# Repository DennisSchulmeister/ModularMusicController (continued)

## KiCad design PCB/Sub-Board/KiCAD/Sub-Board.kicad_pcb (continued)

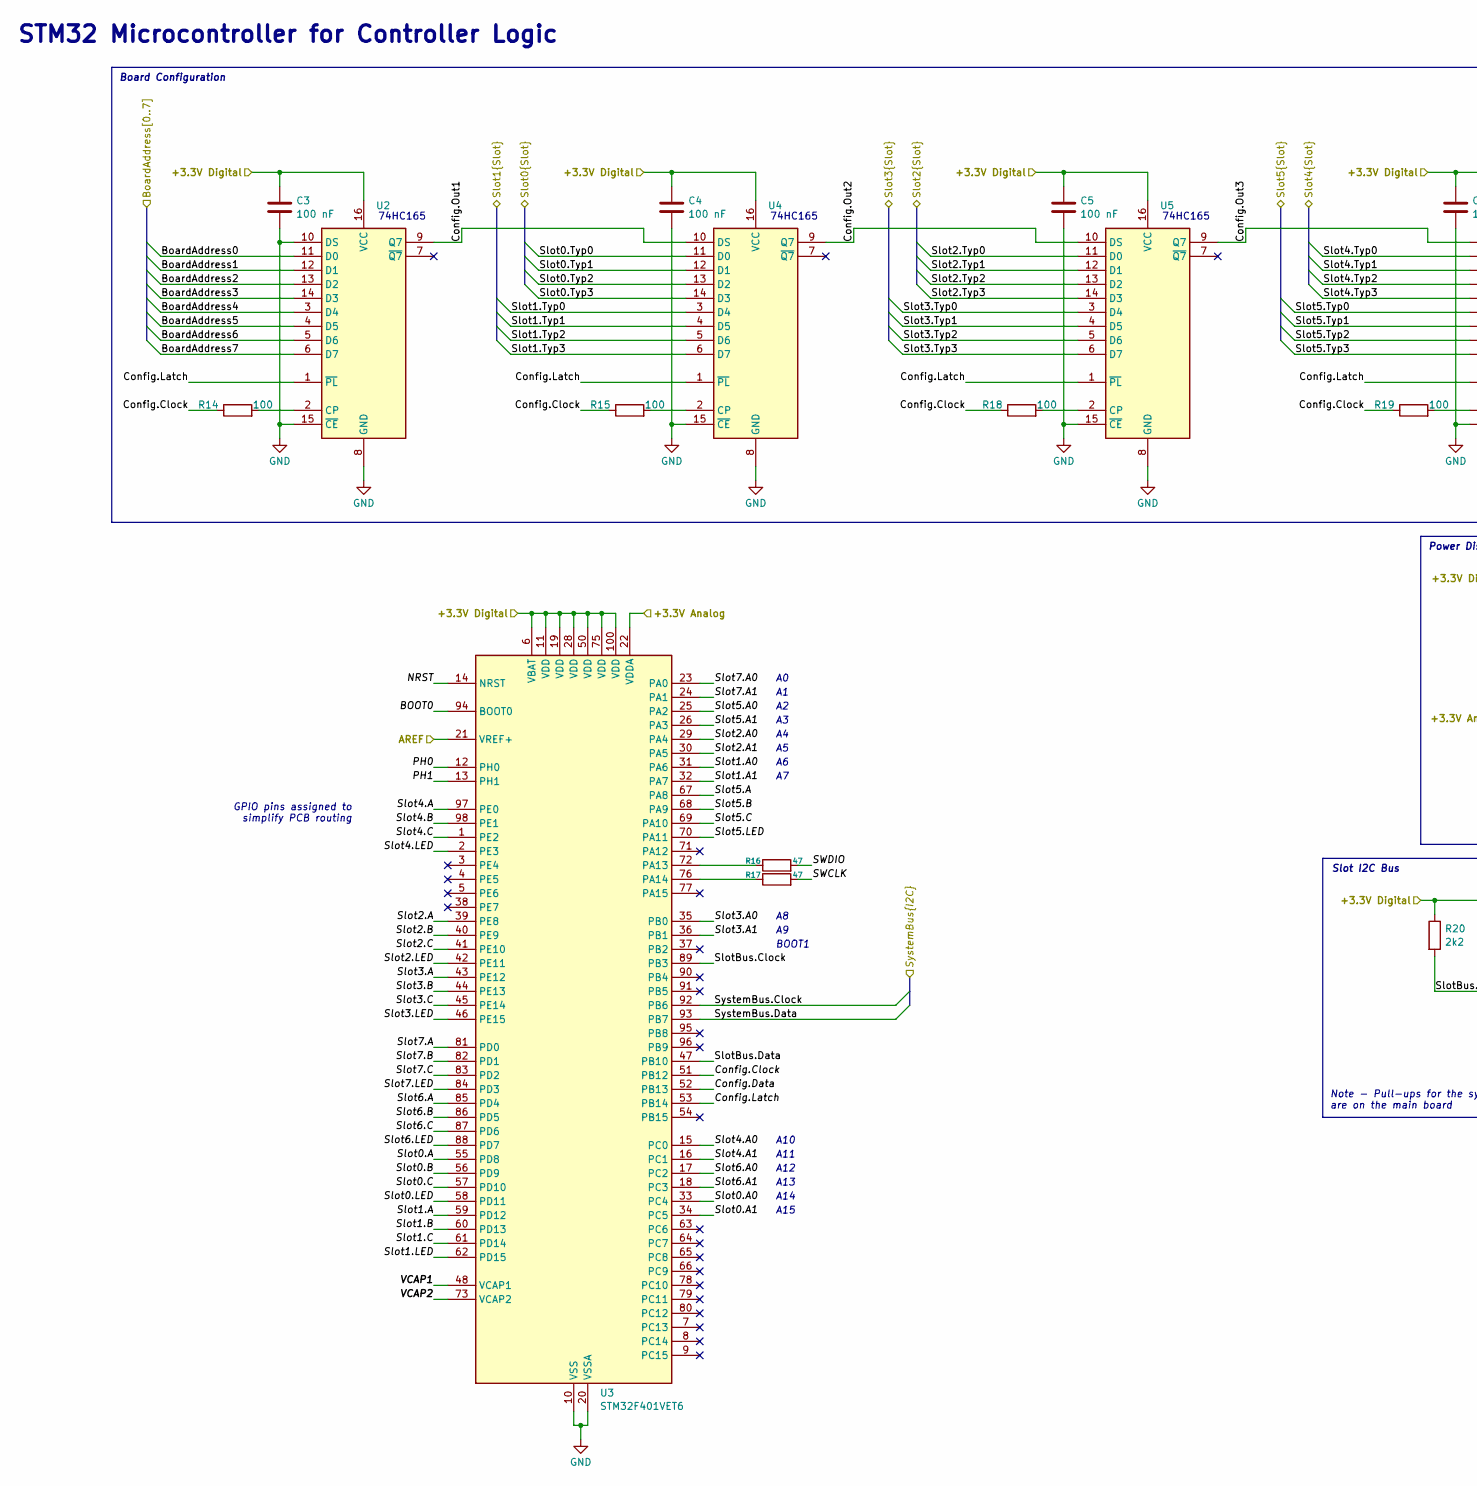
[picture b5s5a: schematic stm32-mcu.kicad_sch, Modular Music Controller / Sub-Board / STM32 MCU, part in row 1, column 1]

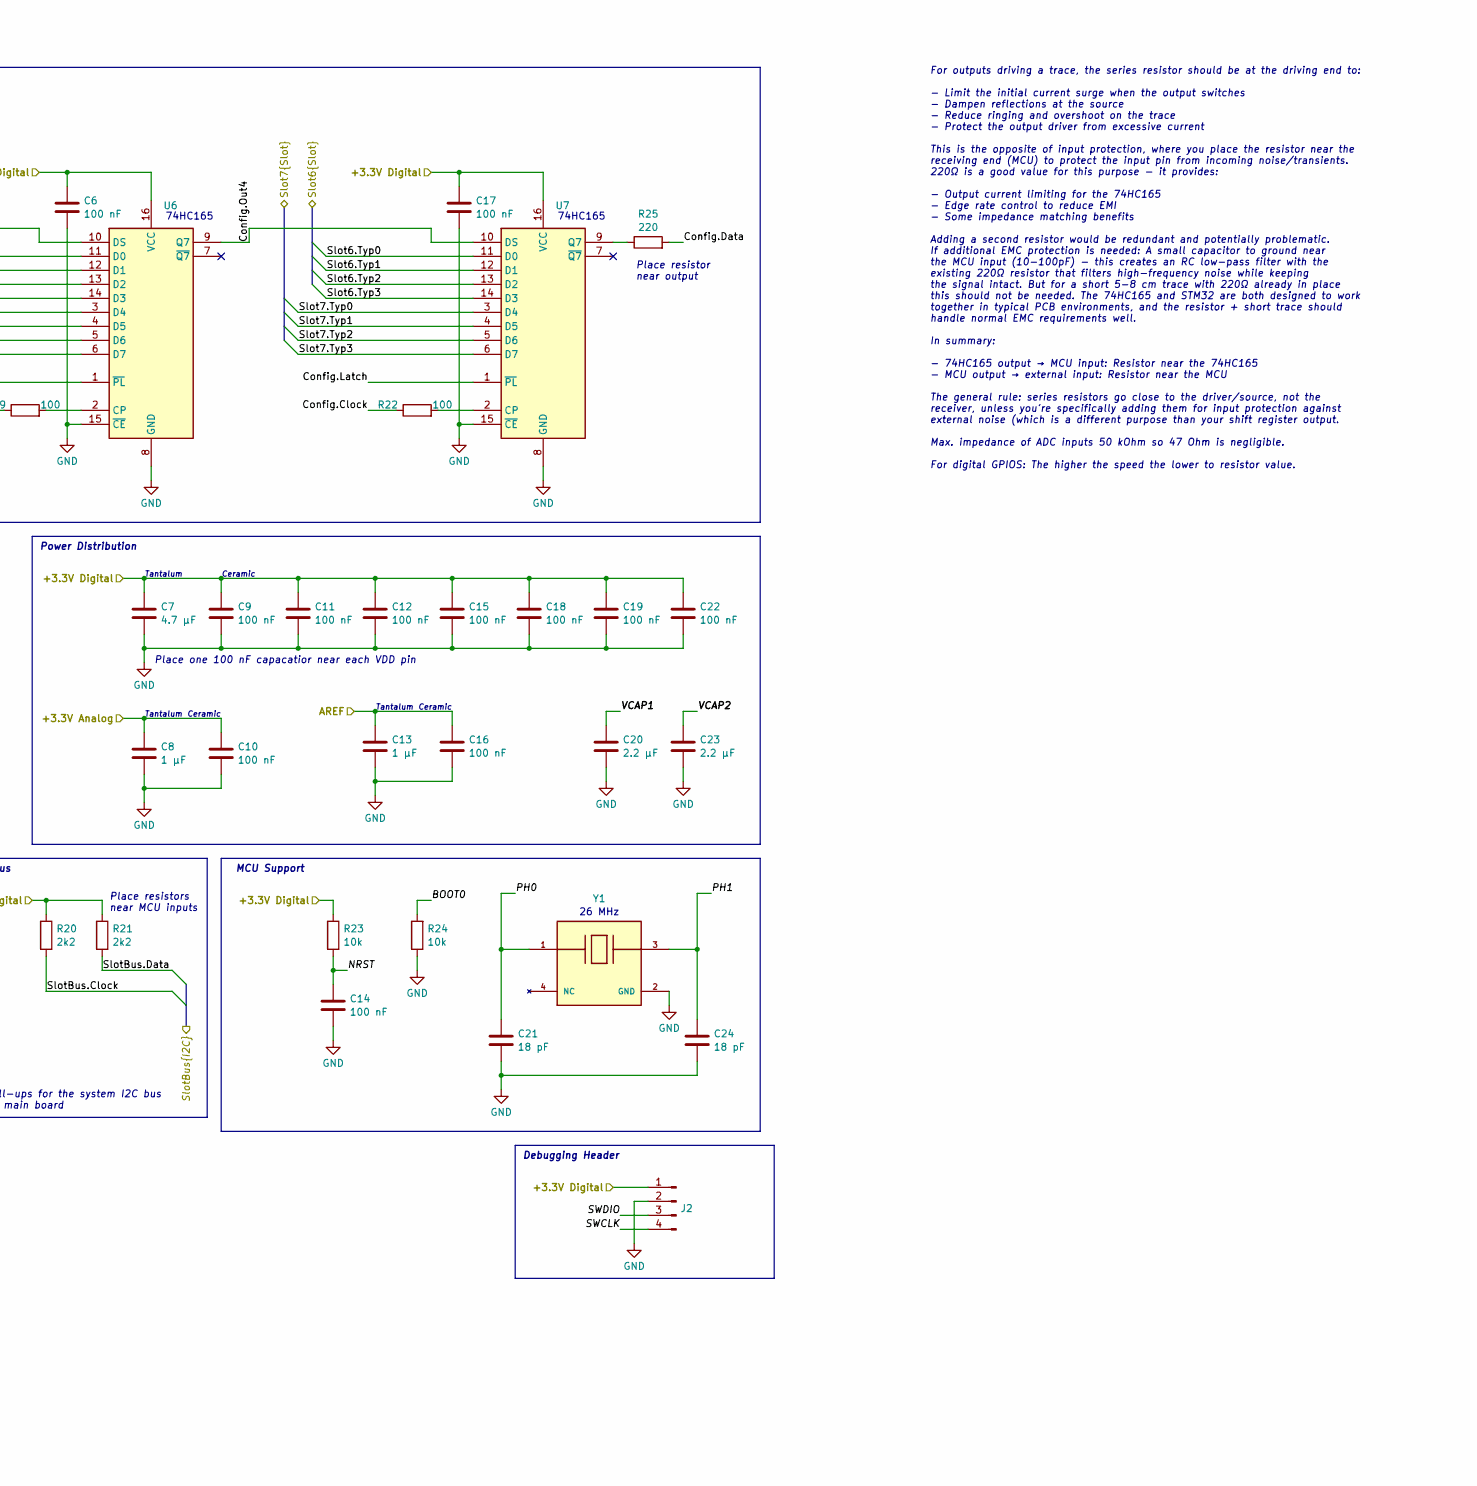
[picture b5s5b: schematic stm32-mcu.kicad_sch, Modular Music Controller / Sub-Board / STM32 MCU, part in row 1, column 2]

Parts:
C3, C4, C5, C6, C9, C10, C11, C12, C14, C15, C16, C17, C18, C19, C22: 100 nF; C_0603_1608Metric
C7: 4.7 µF; C_0805_2012Metric
C8, C13: 1 µF; C_0805_2012Metric
C20, C23: 2.2 µF; C_0805_2012Metric
C21, C24: 18 pF; C_0603_1608Metric
J2: Harwin M20-8770446; PinHeader_1x04_P2.54mm_Vertical_SMD_Pin1Right
R14, R15, R18, R19, R22: 100; R_0402_1005Metric
R16, R17: 47; R_0402_1005Metric
R20, R21: 2k2; R_0402_1005Metric
R23, R24: 10k; R_0402_1005Metric
R25: 220; R_0402_1005Metric
U2, U4, U5, U6, U7: Nexperia 74HC165PW,118; TSSOP-16_4.4x5mm_P0.65mm
U3: STM32F401VET6; LQFP-100_14x14mm_P0.5mm
Y1: Kyocera CX2016DB26000H0FLJC2; OSC_CX2016DB26000H0FLJC2; PARTREV October 2024

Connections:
/Board Address/+3.3V Digital: C3.1, C4.1, C5.1, C6.1, C7.1, C9.1, C11.1, C12.1, C15.1, C17.1, C18.1, C19.1, C22.1, J2.1, R20.1, R21.1, R23.1, U2.16 (VCC), U3.6 (VBAT), U3.11 (VDD), U3.19 (VDD), U3.28 (VDD), U3.50 (VDD), U3.75 (VDD), U3.100 (VDD), U4.16 (VCC), U5.16 (VCC), U6.16 (VCC), U7.16 (VCC); also elsewhere on the board
/Board Address/BoardAddress0: U2.11 (D0); also elsewhere on the board
/Board Address/BoardAddress1: U2.12 (D1); also elsewhere on the board
/Board Address/BoardAddress2: U2.13 (D2); also elsewhere on the board
/Board Address/BoardAddress3: U2.14 (D3); also elsewhere on the board
/Board Address/BoardAddress4: U2.3 (D4); also elsewhere on the board
/Board Address/BoardAddress5: U2.4 (D5); also elsewhere on the board
/Board Address/BoardAddress6: U2.5 (D6); also elsewhere on the board
/Board Address/BoardAddress7: U2.6 (D7); also elsewhere on the board
/Power Supply/+3.3V Analog: C8.1, C10.1, U3.22 (VDDA); also elsewhere on the board
/Power Supply/AREF: C13.1, C16.1, U3.21 (VREF+); also elsewhere on the board
/STM32-MCU/BOOT0: R24.2, U3.94 (BOOT0)
/STM32-MCU/Config.Clock: R14.1, R15.1, R18.1, R19.1, R22.1, U3.51 (PB12)
/STM32-MCU/Config.Data: R25.2, U3.52 (PB13)
/STM32-MCU/Config.Latch: U2.1 (~PL), U3.53 (PB14), U4.1 (~PL), U5.1 (~PL), U6.1 (~PL), U7.1 (~PL)
/STM32-MCU/Config.Out1: U2.9 (Q7), U4.10 (DS)
/STM32-MCU/Config.Out2: U4.9 (Q7), U5.10 (DS)
/STM32-MCU/Config.Out3: U5.9 (Q7), U6.10 (DS)
/STM32-MCU/Config.Out4: U6.9 (Q7), U7.10 (DS)
/STM32-MCU/NRST: C14.1, R23.2, U3.14 (NRST)
/STM32-MCU/PH0: C21.1, U3.12 (PH0), Y1.1
/STM32-MCU/PH1: C24.1, U3.13 (PH1), Y1.3
/STM32-MCU/SWCLK: J2.4, R17.2
/STM32-MCU/SWDIO: J2.3, R16.2
/STM32-MCU/Slot0.A: U3.55 (PD8); also elsewhere on the board
/STM32-MCU/Slot0.A0: U3.33 (PC4); also elsewhere on the board
/STM32-MCU/Slot0.A1: U3.34 (PC5); also elsewhere on the board
/STM32-MCU/Slot0.B: U3.56 (PD9); also elsewhere on the board
/STM32-MCU/Slot0.C: U3.57 (PD10); also elsewhere on the board
/STM32-MCU/Slot0.LED: U3.58 (PD11); also elsewhere on the board
/STM32-MCU/Slot0.Typ0: U4.11 (D0); also elsewhere on the board
/STM32-MCU/Slot0.Typ1: U4.12 (D1); also elsewhere on the board
/STM32-MCU/Slot0.Typ2: U4.13 (D2); also elsewhere on the board
/STM32-MCU/Slot0.Typ3: U4.14 (D3); also elsewhere on the board
/STM32-MCU/Slot1.A: U3.59 (PD12); also elsewhere on the board
/STM32-MCU/Slot1.A0: U3.31 (PA6); also elsewhere on the board
/STM32-MCU/Slot1.A1: U3.32 (PA7); also elsewhere on the board
/STM32-MCU/Slot1.B: U3.60 (PD13); also elsewhere on the board
/STM32-MCU/Slot1.C: U3.61 (PD14); also elsewhere on the board
/STM32-MCU/Slot1.LED: U3.62 (PD15); also elsewhere on the board
/STM32-MCU/Slot1.Typ0: U4.3 (D4); also elsewhere on the board
/STM32-MCU/Slot1.Typ1: U4.4 (D5); also elsewhere on the board
/STM32-MCU/Slot1.Typ2: U4.5 (D6); also elsewhere on the board
/STM32-MCU/Slot1.Typ3: U4.6 (D7); also elsewhere on the board
/STM32-MCU/Slot2.A: U3.39 (PE8); also elsewhere on the board
/STM32-MCU/Slot2.A0: U3.29 (PA4); also elsewhere on the board
/STM32-MCU/Slot2.A1: U3.30 (PA5); also elsewhere on the board
/STM32-MCU/Slot2.B: U3.40 (PE9); also elsewhere on the board
/STM32-MCU/Slot2.C: U3.41 (PE10); also elsewhere on the board
/STM32-MCU/Slot2.LED: U3.42 (PE11); also elsewhere on the board
/STM32-MCU/Slot2.Typ0: U5.11 (D0); also elsewhere on the board
/STM32-MCU/Slot2.Typ1: U5.12 (D1); also elsewhere on the board
/STM32-MCU/Slot2.Typ2: U5.13 (D2); also elsewhere on the board
/STM32-MCU/Slot2.Typ3: U5.14 (D3); also elsewhere on the board
/STM32-MCU/Slot3.A: U3.43 (PE12); also elsewhere on the board
/STM32-MCU/Slot3.A0: U3.35 (PB0); also elsewhere on the board
/STM32-MCU/Slot3.A1: U3.36 (PB1); also elsewhere on the board
/STM32-MCU/Slot3.B: U3.44 (PE13); also elsewhere on the board
/STM32-MCU/Slot3.C: U3.45 (PE14); also elsewhere on the board
/STM32-MCU/Slot3.LED: U3.46 (PE15); also elsewhere on the board
/STM32-MCU/Slot3.Typ0: U5.3 (D4); also elsewhere on the board
/STM32-MCU/Slot3.Typ1: U5.4 (D5); also elsewhere on the board
/STM32-MCU/Slot3.Typ2: U5.5 (D6); also elsewhere on the board
/STM32-MCU/Slot3.Typ3: U5.6 (D7); also elsewhere on the board
/STM32-MCU/Slot4.A: U3.97 (PE0); also elsewhere on the board
/STM32-MCU/Slot4.A0: U3.15 (PC0); also elsewhere on the board
/STM32-MCU/Slot4.A1: U3.16 (PC1); also elsewhere on the board
/STM32-MCU/Slot4.B: U3.98 (PE1); also elsewhere on the board
/STM32-MCU/Slot4.C: U3.1 (PE2); also elsewhere on the board
/STM32-MCU/Slot4.LED: U3.2 (PE3); also elsewhere on the board
/STM32-MCU/Slot4.Typ0: U6.11 (D0); also elsewhere on the board
/STM32-MCU/Slot4.Typ1: U6.12 (D1); also elsewhere on the board
/STM32-MCU/Slot4.Typ2: U6.13 (D2); also elsewhere on the board
/STM32-MCU/Slot4.Typ3: U6.14 (D3); also elsewhere on the board
/STM32-MCU/Slot5.A: U3.67 (PA8); also elsewhere on the board
/STM32-MCU/Slot5.A0: U3.25 (PA2); also elsewhere on the board
/STM32-MCU/Slot5.A1: U3.26 (PA3); also elsewhere on the board
/STM32-MCU/Slot5.B: U3.68 (PA9); also elsewhere on the board
/STM32-MCU/Slot5.C: U3.69 (PA10); also elsewhere on the board
/STM32-MCU/Slot5.LED: U3.70 (PA11); also elsewhere on the board
/STM32-MCU/Slot5.Typ0: U6.3 (D4); also elsewhere on the board
/STM32-MCU/Slot5.Typ1: U6.4 (D5); also elsewhere on the board
/STM32-MCU/Slot5.Typ2: U6.5 (D6); also elsewhere on the board
/STM32-MCU/Slot5.Typ3: U6.6 (D7); also elsewhere on the board
/STM32-MCU/Slot6.A: U3.85 (PD4); also elsewhere on the board
/STM32-MCU/Slot6.A0: U3.17 (PC2); also elsewhere on the board
/STM32-MCU/Slot6.A1: U3.18 (PC3); also elsewhere on the board
/STM32-MCU/Slot6.B: U3.86 (PD5); also elsewhere on the board
/STM32-MCU/Slot6.C: U3.87 (PD6); also elsewhere on the board
/STM32-MCU/Slot6.LED: U3.88 (PD7); also elsewhere on the board
/STM32-MCU/Slot6.Typ0: U7.11 (D0); also elsewhere on the board
/STM32-MCU/Slot6.Typ1: U7.12 (D1); also elsewhere on the board
/STM32-MCU/Slot6.Typ2: U7.13 (D2); also elsewhere on the board
/STM32-MCU/Slot6.Typ3: U7.14 (D3); also elsewhere on the board
/STM32-MCU/Slot7.A: U3.81 (PD0); also elsewhere on the board
/STM32-MCU/Slot7.A0: U3.23 (PA0); also elsewhere on the board
/STM32-MCU/Slot7.A1: U3.24 (PA1); also elsewhere on the board
/STM32-MCU/Slot7.B: U3.82 (PD1); also elsewhere on the board
/STM32-MCU/Slot7.C: U3.83 (PD2); also elsewhere on the board
/STM32-MCU/Slot7.LED: U3.84 (PD3); also elsewhere on the board
/STM32-MCU/Slot7.Typ0: U7.3 (D4); also elsewhere on the board
/STM32-MCU/Slot7.Typ1: U7.4 (D5); also elsewhere on the board
/STM32-MCU/Slot7.Typ2: U7.5 (D6); also elsewhere on the board
/STM32-MCU/Slot7.Typ3: U7.6 (D7); also elsewhere on the board
/STM32-MCU/SlotBus.Clock: R20.2, U3.89 (PB3); also elsewhere on the board
/STM32-MCU/SlotBus.Data: R21.2, U3.47 (PB10); also elsewhere on the board
/STM32-MCU/SystemBus.Clock: U3.92 (PB6); also elsewhere on the board
/STM32-MCU/SystemBus.Data: U3.93 (PB7); also elsewhere on the board
/STM32-MCU/VCAP1: C20.1, U3.48 (VCAP1)
/STM32-MCU/VCAP2: C23.1, U3.73 (VCAP2)
GND: C3.2, C4.2, C5.2, C6.2, C7.2, C8.2, C9.2, C10.2, C11.2, C12.2, C13.2, C14.2, C15.2, C16.2, C17.2, C18.2, C19.2, C20.2, C21.2, C22.2, C23.2, C24.2, J2.2, R24.1, U2.8 (GND), U2.10 (DS), U2.15 (~CE), U3.10 (VSS), U3.20 (VSSA), U3.27 (VSS), U3.49 (VSS), U3.74 (VSS), U3.99 (VSS), U4.8 (GND), U4.15 (~CE), U5.8 (GND), U5.15 (~CE), U6.8 (GND), U6.15 (~CE), U7.8 (GND), U7.15 (~CE), Y1.2 (GND); also elsewhere on the board
unnamed: R14.2, U2.2 (CP)
unnamed: R16.1, U3.72 (PA13)
unnamed: R17.1, U3.76 (PA14)
unnamed: R15.2, U4.2 (CP)
unnamed: R18.2, U5.2 (CP)
unnamed: R19.2, U6.2 (CP)
unnamed: R22.2, U7.2 (CP)
unnamed: R25.1, U7.9 (Q7)

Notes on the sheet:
74HC165
Place resistor near output
Place resistors near MCU inputs
Power Distribution
For outputs driving a trace, the series resistor should be at the driving end to: - Limit the initial current surge when the output switches - Dampen reflections at the source - Reduce ringing and overshoot on the trace - Protect the output driver from excessive current This is the opposite of inpu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
Debugging Header
Tantalum
A12
Board Configuration
A10
Ceramic
GPIO pins assigned to simplify PCB routing
A14
A15
Place one 100 nF capacatior near each VDD pin
STM32 Microcontroller for Controller Logic
MCU Support
Slot I2C Bus
A13
A11
BOOT1
Note - Pull-ups for the system I2C bus are on the main board
26 MHz

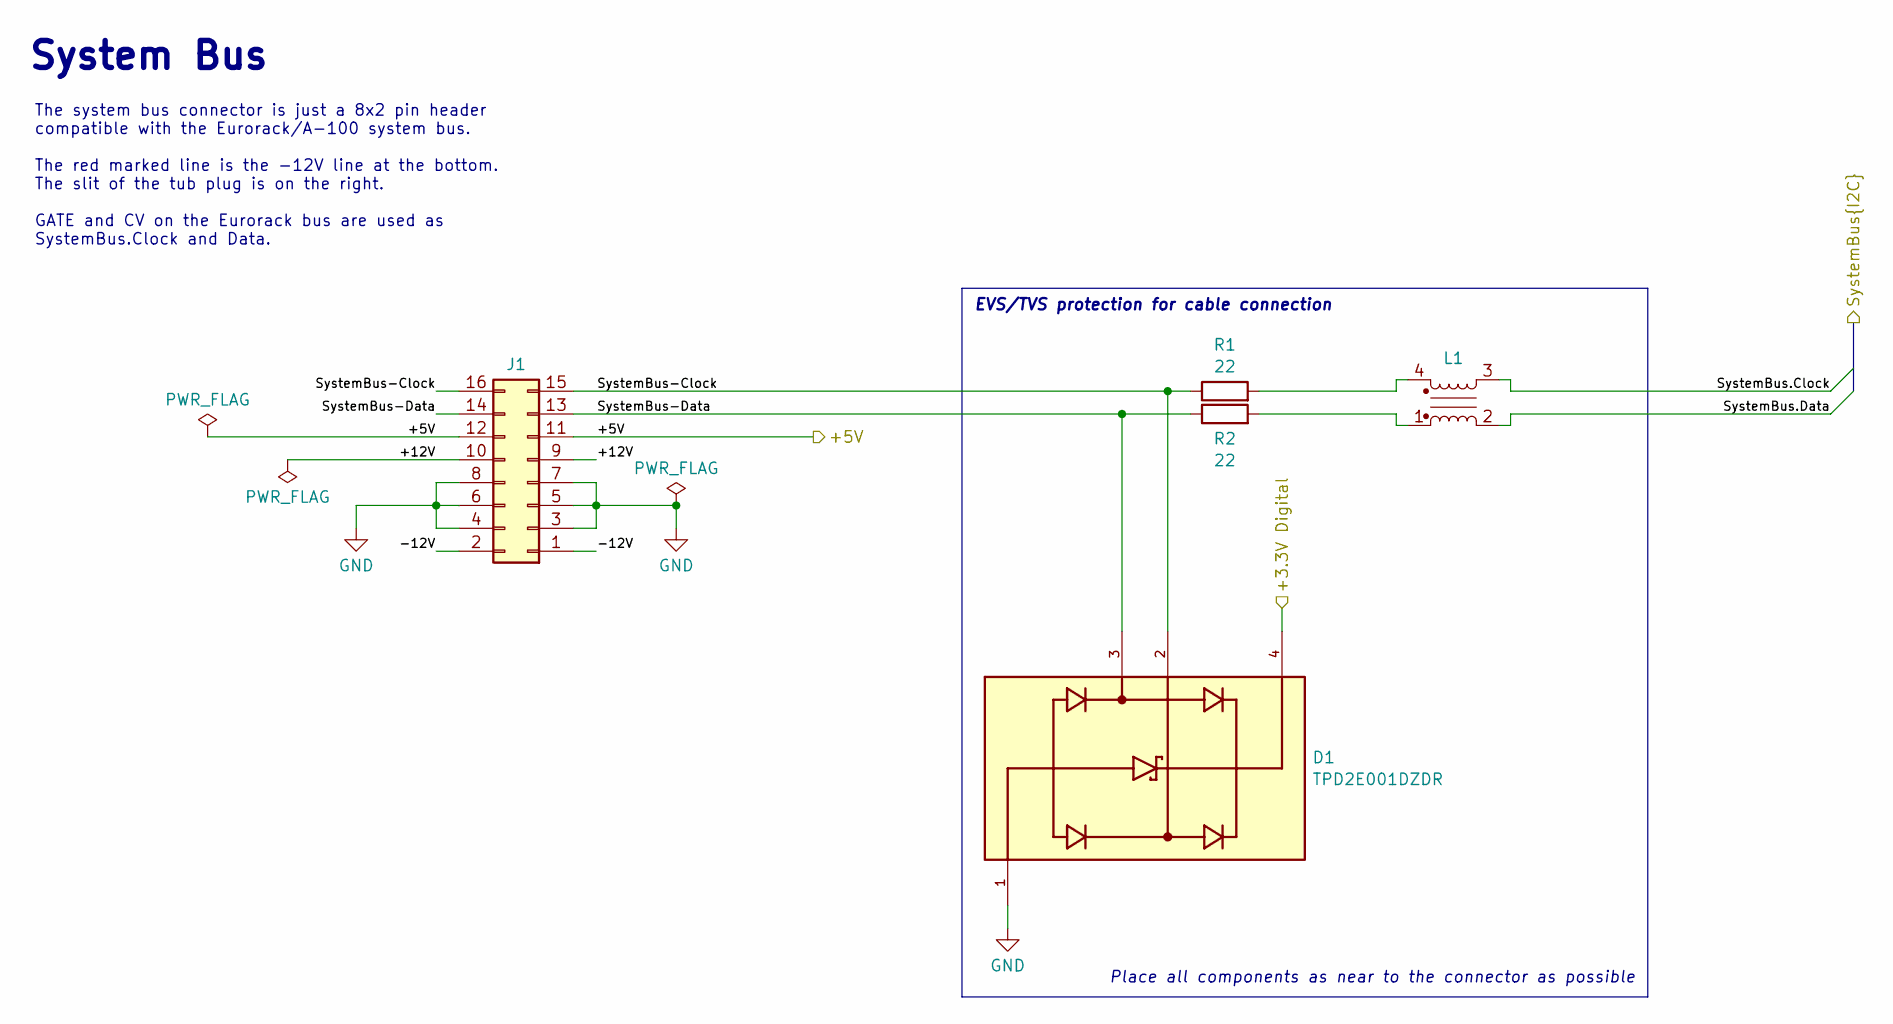
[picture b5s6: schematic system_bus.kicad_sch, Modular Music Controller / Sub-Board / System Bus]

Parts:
D1: TPD2E001DZDR; SOT192P237X122-4N; PARTREV I
J1: Harwin M20-8760846; PinHeader_2x08_P2.54mm_Vertical_SMD
L1: Wuerth 744232090; L_CommonMode_Wurth_WE-CNSW-1206
R1, R2: 22; R_0402_1005Metric

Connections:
/Board Address/+3.3V Digital: D1.4; also elsewhere on the board
/STM32-MCU/SystemBus.Clock: L1.3; also elsewhere on the board
/STM32-MCU/SystemBus.Data: L1.2; also elsewhere on the board
/System Bus/+5V: J1.11, J1.12; also elsewhere on the board
/System Bus/+12V: J1.9, J1.10
/System Bus/-12V: J1.1, J1.2
/System Bus/SystemBus-Clock: D1.2, J1.15, J1.16, R1.1
/System Bus/SystemBus-Data: D1.3, J1.13, J1.14, R2.1
GND: D1.1, J1.3, J1.4, J1.5, J1.6, J1.7, J1.8; also elsewhere on the board
unnamed: L1.1, R2.2
unnamed: L1.4, R1.2

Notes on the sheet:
EVS/TVS protection for cable connection
The system bus connector is just a 8x2 pin header compatible with the Eurorack/A-100 system bus. The red marked line is the -12V line at the bottom. The slit of the tub plug is on the right. GATE and CV on the Eurorack bus are used as SystemBus.Clock and Data.
System Bus
Place all components as near to the connector as possible

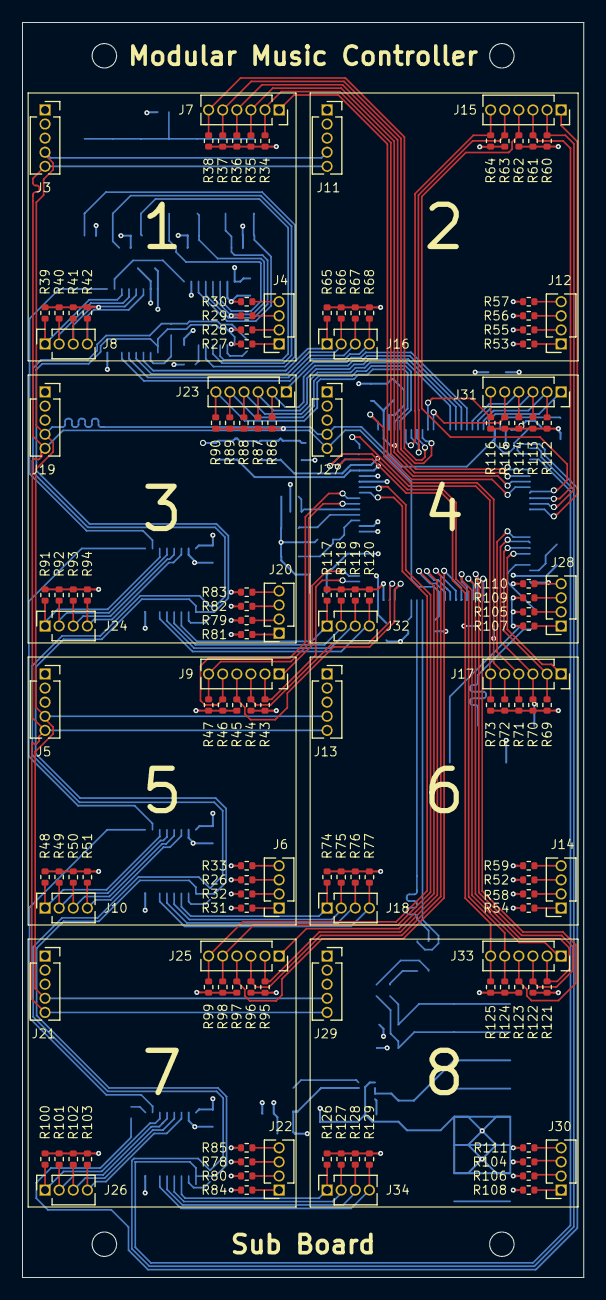
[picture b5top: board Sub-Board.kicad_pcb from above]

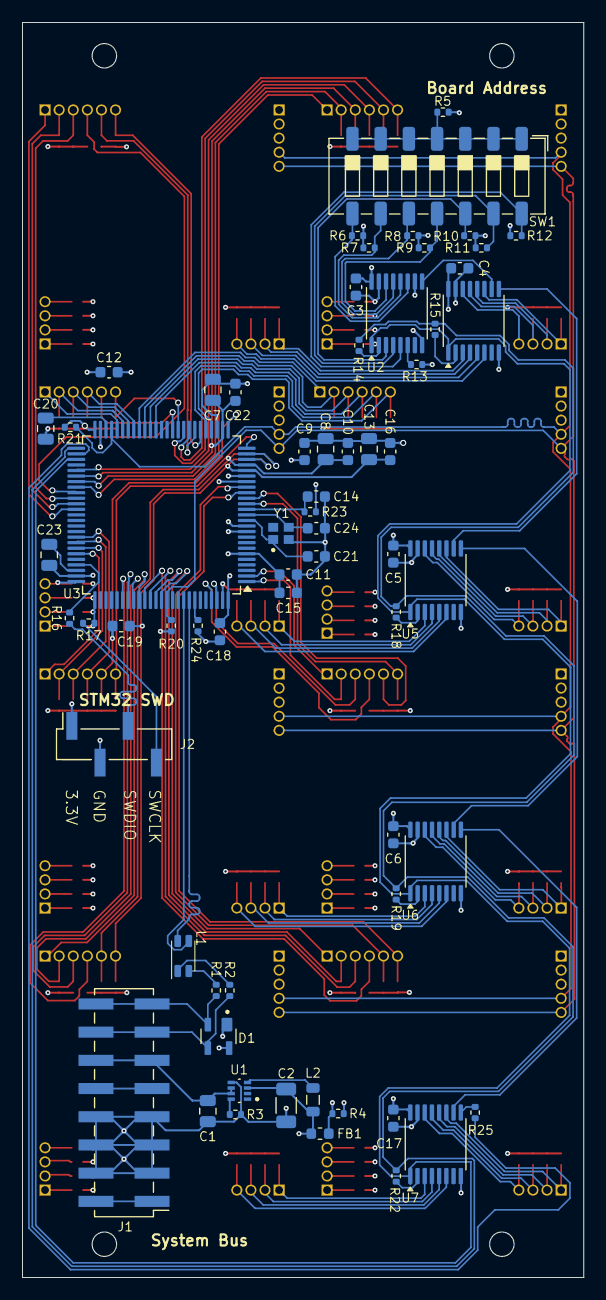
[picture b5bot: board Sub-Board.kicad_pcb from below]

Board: 4 copper layers, 50.5 x 113.0 mm, 200 parts (64 on the bottom side), 161 nets.

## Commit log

2025-09-21 Minimal PlatformIO project structure
2025-09-27 LCD-Board experiment: Initial code
2025-09-29 More fun with rotary encoders
2025-09-29 Experiments: README.md table fix and .gitkeep files
2025-09-29 Silly GitHub flavoured markdown table syntax!
2025-09-30 Experiment LCD-Board: Schematic and better ISR
2025-10-01 New experiment foreseen: ESP32-Webserver
2025-10-01 LCD-Board: Typos in schematic
2025-10-01 LCD-Board: Better screen update strategy
2025-10-02 ESP32-Webserver: Begin of experiment
2025-10-02 Small README.md fixes
2025-10-04 Update project layout for easier VS Code editing
2025-10-04 VS Code + PlatfromIO IDE again
2025-10-05 ESP32-Webserver: Filesystem mounts
2025-10-05 ESP32-Webserver: IFF files (wip)
2025-10-10 Firmware: Rename controller to sub board
2025-10-11 Webconfig: Mock server
2025-10-11 Experiments (wip)
2025-10-11 Webconfig: Add license headers
2025-10-11 Webconfig: Small typo
2025-10-11 Webconfig: Esbuild
2025-10-11 Webconfig: First deployment test
2025-10-11 Webconfig: Bootstrap and HTMX (wip)
2025-10-11 CRLF test
2025-10-11 Webconfig: HTMX page loads
2025-10-12 Webclient: Wifi endpoints, hamburger button
2025-10-12 Webclient: API updates
2025-10-12 Webconfig: Refactor types
2025-10-13 Webconfig: Popup component
2025-10-13 Webconfig: Skip rather huge codemaps during deployment
2025-10-13 Webconfig: Device settings UI
2025-10-13 Webconfig: Alpine.js fixes
2025-10-13 Webconfig: Merge APIs for control general and control ranges
2025-10-13 Webconfig: Replace HTMX dependency
2025-10-13 Webconfig: Predefined baud rates
2025-10-13 Webclient: WiFi settings (wip)
2025-10-13 Webconfig: WiFi settings finished
2025-10-13 Webclient: Prevent data-loss due to navigation
2025-10-14 Webconfig: MQTT table (wip)
2025-10-15 Webconfig: Config tables for OSC and MQTT
2025-10-15 Webconfig: Control pages, export/import (wip)
2025-10-16 Webconfig: Single Control templates
2025-10-16 Webconfig: Import settings + backend fixes
2025-10-16 Webconfig: Fix incomplete import of control messages
2025-10-21 Webconfig: OSC Messages (wip)
2025-10-21 Webconfig: OSC Messages
2025-10-21 Webconfig: Fetch OSC servers
2025-10-21 ESP32-Webserver: IFF Reader/Writer (wip)
2025-10-21 package.json geändert wegen Windows, die vier besprochenen Seiten haben jetzt eine Logik
2025-10-27 Webconfig: Various fixes
2025-10-27 ESP32-Webserver: IFF_Writer
2025-10-27 ESP32-Webserver: noexcept
2025-10-27 ESP32-Webserver: Improved filesystem API
2025-10-28 ESP32-Webserver: WiFi (wip)
2025-10-28 ESP32-Webserver: WiFi (untested yet)
2025-10-28 ESP32-Webserver: Fix compiler and linker errors
2025-10-28 ESP32-Webserver: Fix mount errors
2025-10-29 ESP32-Webserver: WiFi STA debugging
2025-11-08 ESP32-Webserver: Forgotten commit
2025-11-08 PCB-Layout for sub-board (wip)
2025-11-09 Sub-Board PCB before ERC
2025-11-09 Sub-Board PCB after ERC
2025-11-09 Sub-Board PCB: I2C Busses
2025-11-10 Sub-Board PCB: Footprint assignments
2025-11-11 Sub Board PCB: PCB Layout (wip)
2025-11-11 Sub Board PCB: Parts Placement (wip)
2025-11-11 Sub Board PCB: Placement finished
2025-11-11 Sub Board PCB: Pin Connectors
2025-11-11 Sub Board PCB: GND/GNDD
2025-11-11 Sub Board PCB: Netclass assignments
2025-11-11 Sub Board PCB: Board Setup
2025-11-11 Sub Board PCB: Fix silkscreen size
2025-11-12 Sub Board PCB: Routing (wip)
2025-11-12 Sub Board PCB: Power routing
2025-11-12 Sub Board PCB: Power and Slot I2C Routing
2025-11-12 Sub Board PCB: More Routing
2025-11-24 Sub Board PCB: Better component placement
2025-11-29 Sub Board PCB: Slot2 routing
2025-11-30 Sub Board PCB: Slot routing (wip)
2025-11-30 Sub Board: Finished routing with DRC
2025-11-30 KiCad lock files
2025-11-30 Sub Board: Gerber and BOM files
2025-12-01 Sub Board: Export files
2025-12-01 Better PCB directory layout
2025-12-02 PCB Sub Board: Revision 2
2025-12-02 PCB Block Simple Switch (wip)
2025-12-02 PCB Block Simple Switch (finished)
2025-12-02 Block Simple Switch → Block Switch 1
2025-12-03 PCBs for different blocks
2025-12-11 Add bottom view picture for each PCB
